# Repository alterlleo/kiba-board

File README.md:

# kiba-board
Truffle finder board

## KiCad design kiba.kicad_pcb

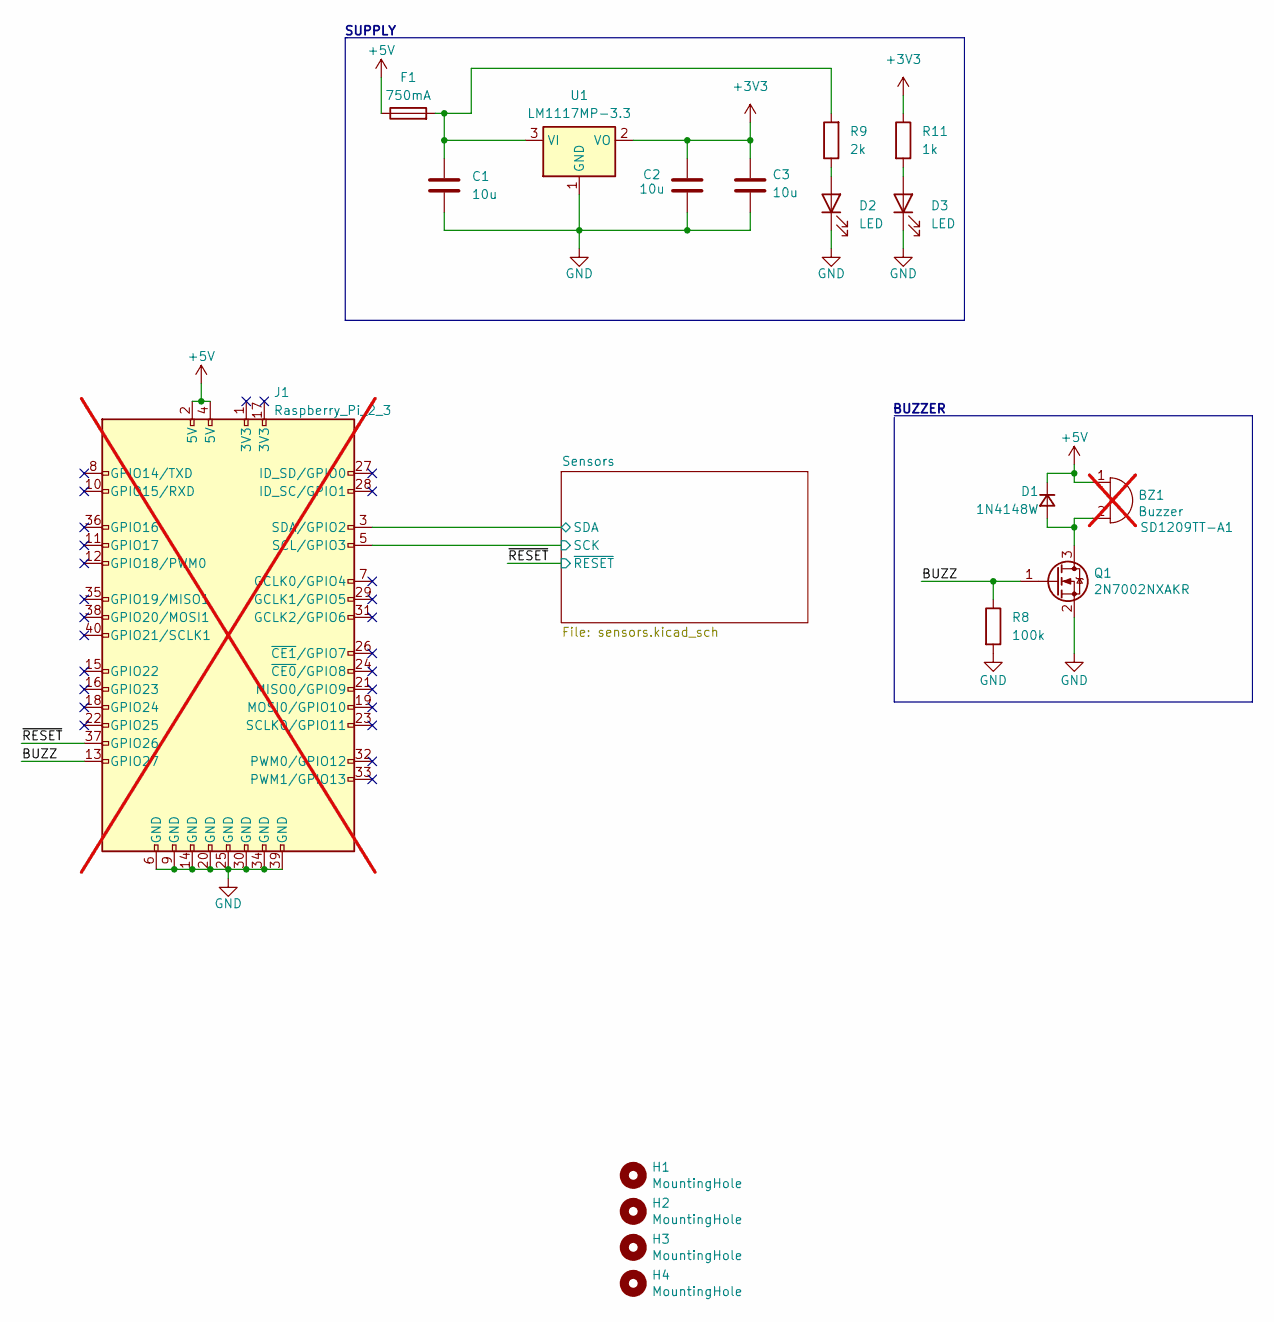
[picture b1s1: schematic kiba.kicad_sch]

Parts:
BZ1: Buzzer; Buzzer_TDK_PS1240P02BT_D12.2mm_H6.5mm; MPN SD1209TT-A1; LCSC C91083; not fitted
C1, C2, C3: 10u; C_0603_1608Metric
D1: 1N4148W; D_SOD-323_HandSoldering; MPN 1N4148W; LCSC C2099
D2: LED; D_0603_1608Metric; MPN TLMS1000-GS15; LCSC C2288
D3: LED; D_0603_1608Metric; MPN TLMS1000-GS15; LCSC C12624
F1: 750mA; Fuse_0603_1608Metric; LCSC C206991
H1, H2, H3, H4: MountingHole; MountingHole_3.2mm_M3_ISO14580
J1: Raspberry_Pi_2_3; raspberrypi; MPN 2.54-2*20; LCSC C2977589; not fitted
Q1: 2N7002NXAKR; SOT-23; MPN 2N7002NXAKR; LCSC C551416
R8: 100k; R_0603_1608Metric
R9: 2k; R_0603_1608Metric
R11: 1k; R_0603_1608Metric
U1: LM1117MP-3.3; SOT-223-3_TabPin2; MPN LM1117MP-3.3/TR; LCSC C498153

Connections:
+3V3: C2.1, C3.1, R11.1, U1.2 (VO); also elsewhere on the board
+5V: BZ1.1 (-), D1.1 (K), F1.1, J1.2 (5V), J1.4 (5V)
/BUZZ: J1.13 (GPIO27), Q1.1 (G), R8.1
/Sensors/SCK: J1.5 (SCL/GPIO3); also elsewhere on the board
/Sensors/SDA: J1.3 (SDA/GPIO2); also elsewhere on the board
/~RESET: J1.37 (GPIO26); also elsewhere on the board
GND: C1.2, C2.2, C3.2, D2.1 (K), D3.1 (K), J1.6 (GND), J1.9 (GND), J1.14 (GND), J1.20 (GND), J1.25 (GND), J1.30 (GND), J1.34 (GND), J1.39 (GND), Q1.2 (S), R8.2, U1.1 (GND); also elsewhere on the board
unnamed: BZ1.2 (+), D1.2 (A), Q1.3 (D)
unnamed: D2.2 (A), R9.1
unnamed: D3.2 (A), R11.2
unnamed: C1.1, F1.2, R9.2, U1.3 (VI)

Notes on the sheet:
SUPPLY
BUZZER

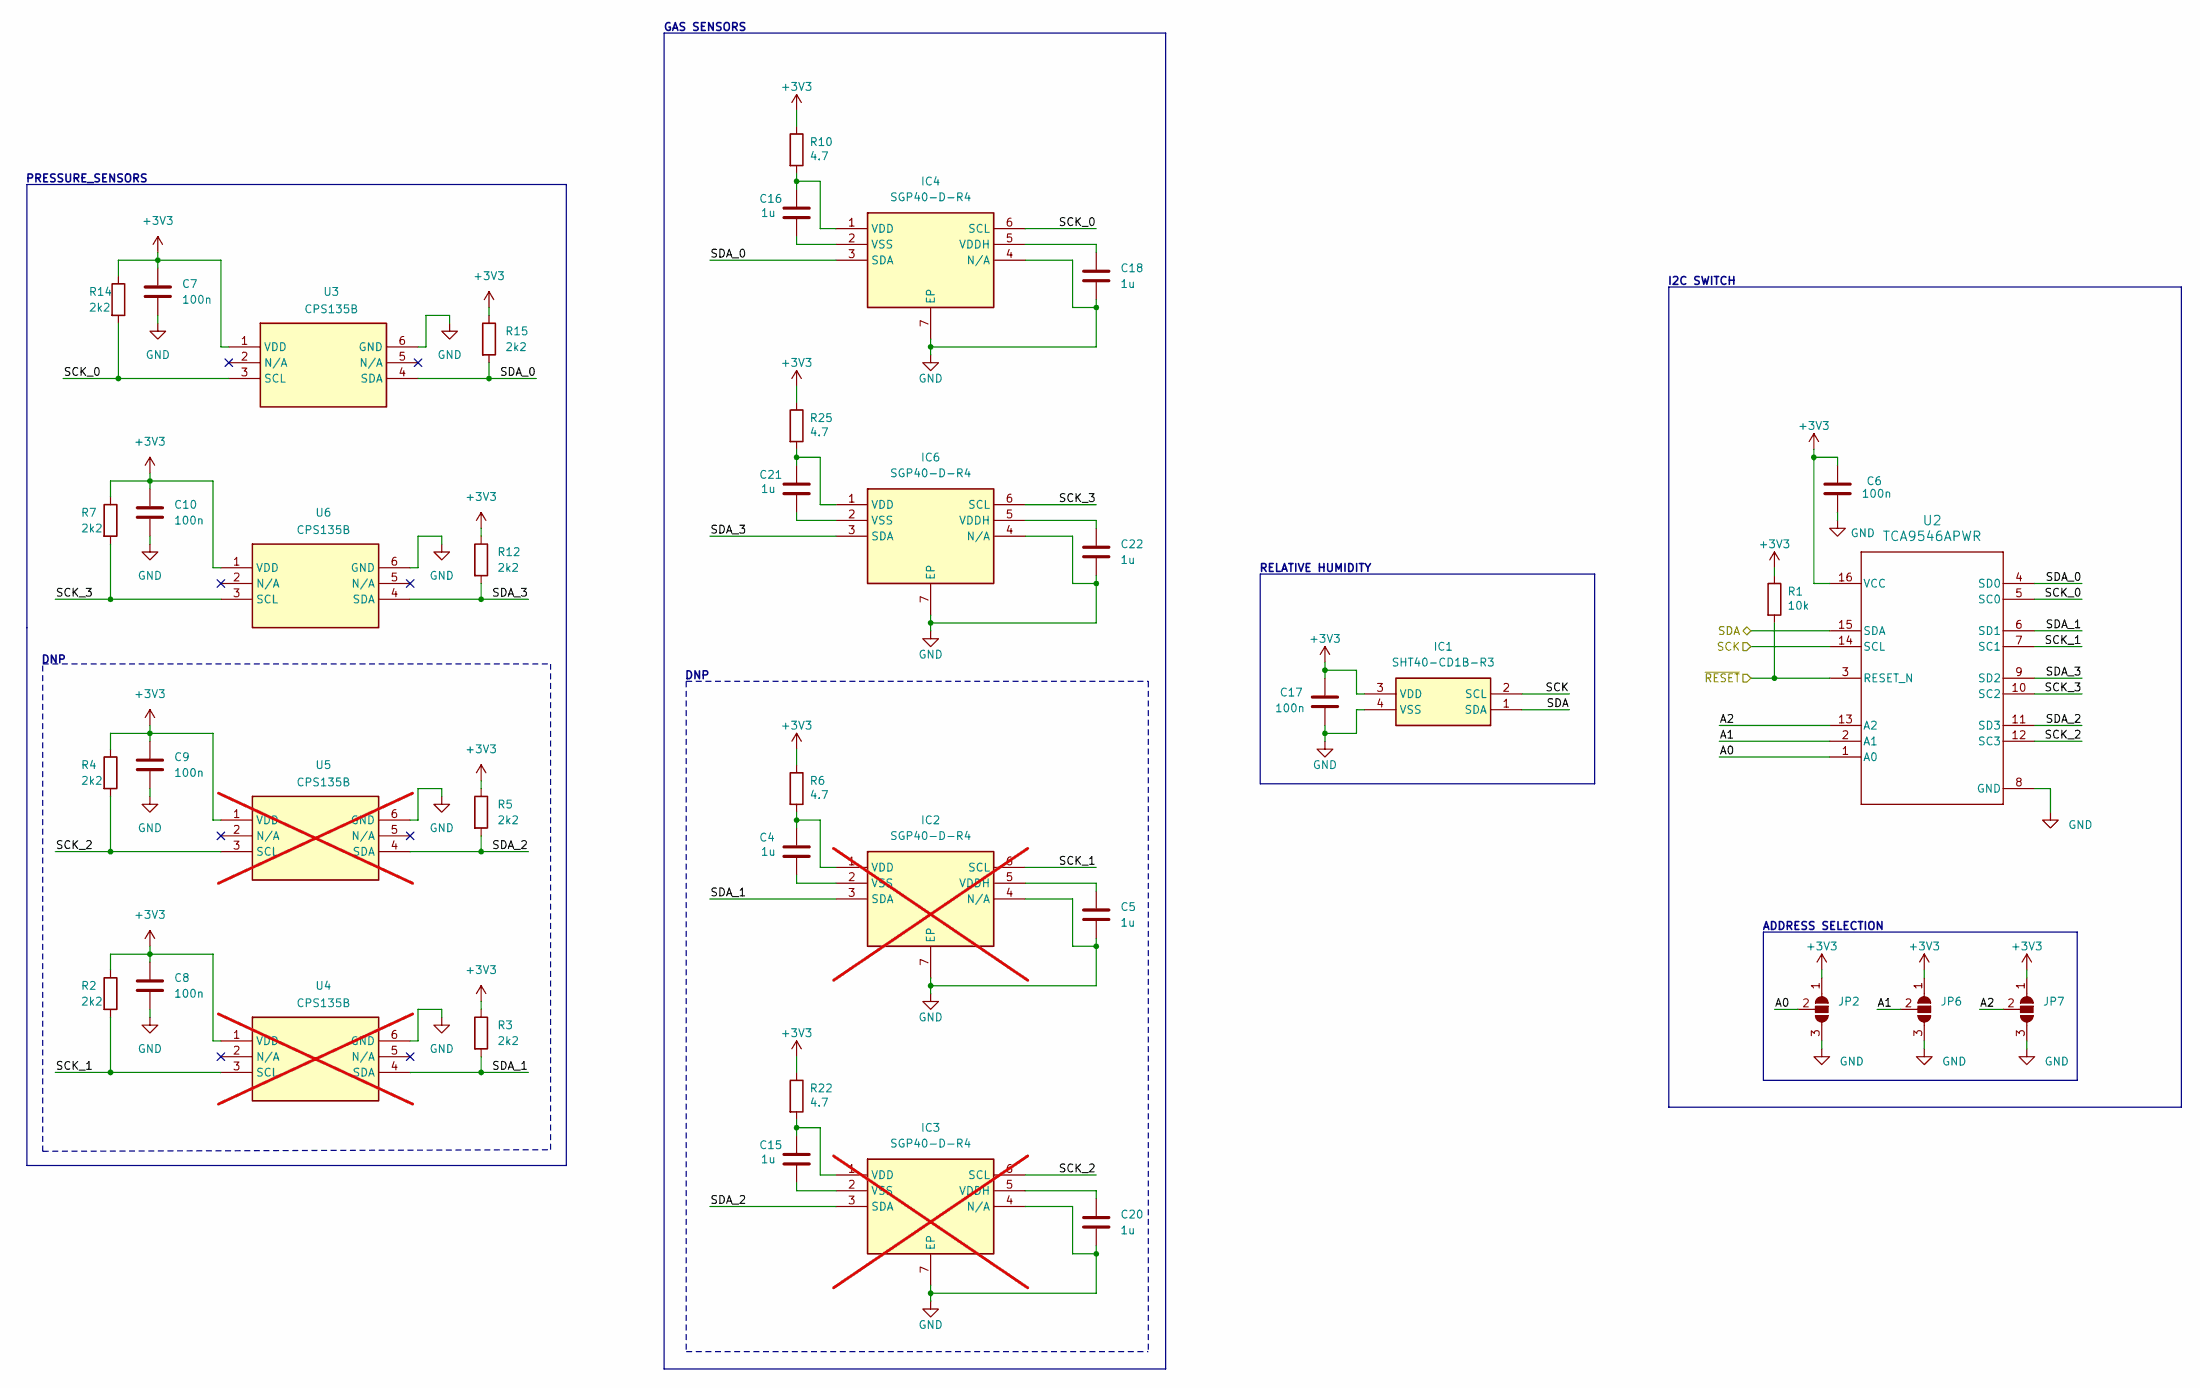
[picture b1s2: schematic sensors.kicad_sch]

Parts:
C4, C5, C15, C16, C18, C20, C21, C22: 1u; C_0603_1608Metric
C6, C7, C8, C9, C10, C17: 100n; C_0603_1608Metric
IC1: SHT40-CD1B-R3; SHT40CD1BR3; Mouser Part Number 403-SHT40-CD1B-R3
IC2, IC3: SGP40-D-R4; SON80P244X244X95-7N; Mouser Part Number 403-SGP40-D-R4; not fitted
IC4, IC6: SGP40-D-R4; SON80P244X244X95-7N; Mouser Part Number 403-SGP40-D-R4
JP2, JP6, JP7: SolderJumper_3_Open; SolderJumper-3_P1.3mm_Open_RoundedPad1.0x1.5mm
R1: 10k; R_0603_1608Metric
R2, R3, R4, R5, R7, R12, R14, R15: 2k2; R_0603_1608Metric
R6, R10, R22, R25: 4.7; R_0603_1608Metric
U2: TCA9546APWR; PW0016A-IPC_A; LCSC C201653
U3, U6: CPS135B; smd6-4.5mm; LCSC C491452
U4, U5: CPS135B; smd6-4.5mm; LCSC C491452; not fitted

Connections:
+3V3: C6.1, C7.1, C8.1, C9.1, C10.1, C17.1, IC1.3 (VDD), JP2.1 (A), JP6.1 (A), JP7.1 (A), R1.1, R2.1, R3.1, R4.1, R5.1, R6.1, R7.1, R10.1, R12.1, R14.1, R15.1, R22.1, R25.1, U2.16 (VCC), U3.1 (VDD), U4.1 (VDD), U5.1 (VDD), U6.1 (VDD); also elsewhere on the board
/Sensors/A0: JP2.2 (C), U2.1 (A0)
/Sensors/A1: JP6.2 (C), U2.2 (A1)
/Sensors/A2: JP7.2 (C), U2.13 (A2)
/Sensors/SCK: IC1.2 (SCL), U2.14 (SCL); also elsewhere on the board
/Sensors/SCK_0: IC4.6 (SCL), R14.2, U2.5 (SC0), U3.3 (SCL)
/Sensors/SCK_1: IC2.6 (SCL), R2.2, U2.7 (SC1), U4.3 (SCL)
/Sensors/SCK_2: IC3.6 (SCL), R4.2, U2.12 (SC3), U5.3 (SCL)
/Sensors/SCK_3: IC6.6 (SCL), R7.2, U2.10 (SC2), U6.3 (SCL)
/Sensors/SDA: IC1.1 (SDA), U2.15 (SDA); also elsewhere on the board
/Sensors/SDA_0: IC4.3 (SDA), R15.2, U2.4 (SD0), U3.4 (SDA)
/Sensors/SDA_1: IC2.3 (SDA), R3.2, U2.6 (SD1), U4.4 (SDA)
/Sensors/SDA_2: IC3.3 (SDA), R5.2, U2.11 (SD3), U5.4 (SDA)
/Sensors/SDA_3: IC6.3 (SDA), R12.2, U2.9 (SD2), U6.4 (SDA)
/~RESET: R1.2, U2.3 (RESET_N); also elsewhere on the board
GND: C5.2, C6.2, C7.2, C8.2, C9.2, C10.2, C17.2, C18.2, C20.2, C22.2, IC1.4 (VSS), IC2.4 (N/A), IC2.7 (EP), IC3.4 (N/A), IC3.7 (EP), IC4.4 (N/A), IC4.7 (EP), IC6.4 (N/A), IC6.7 (EP), JP2.3 (B), JP6.3 (B), JP7.3 (B), U2.8 (GND), U3.6 (GND), U4.6 (GND), U5.6 (GND), U6.6 (GND); also elsewhere on the board
unnamed: C4.1, IC2.1 (VDD), R6.2
unnamed: C5.1, IC2.5 (VDDH)
unnamed: C4.2, IC2.2 (VSS)
unnamed: C15.1, IC3.1 (VDD), R22.2
unnamed: C20.1, IC3.5 (VDDH)
unnamed: C15.2, IC3.2 (VSS)
unnamed: C16.1, IC4.1 (VDD), R10.2
unnamed: C18.1, IC4.5 (VDDH)
unnamed: C16.2, IC4.2 (VSS)
unnamed: C21.1, IC6.1 (VDD), R25.2
unnamed: C22.1, IC6.5 (VDDH)
unnamed: C21.2, IC6.2 (VSS)

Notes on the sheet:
GAS SENSORS
I2C SWITCH
DNP
ADDRESS SELECTION
RELATIVE HUMIDITY
PRESSURE_SENSORS

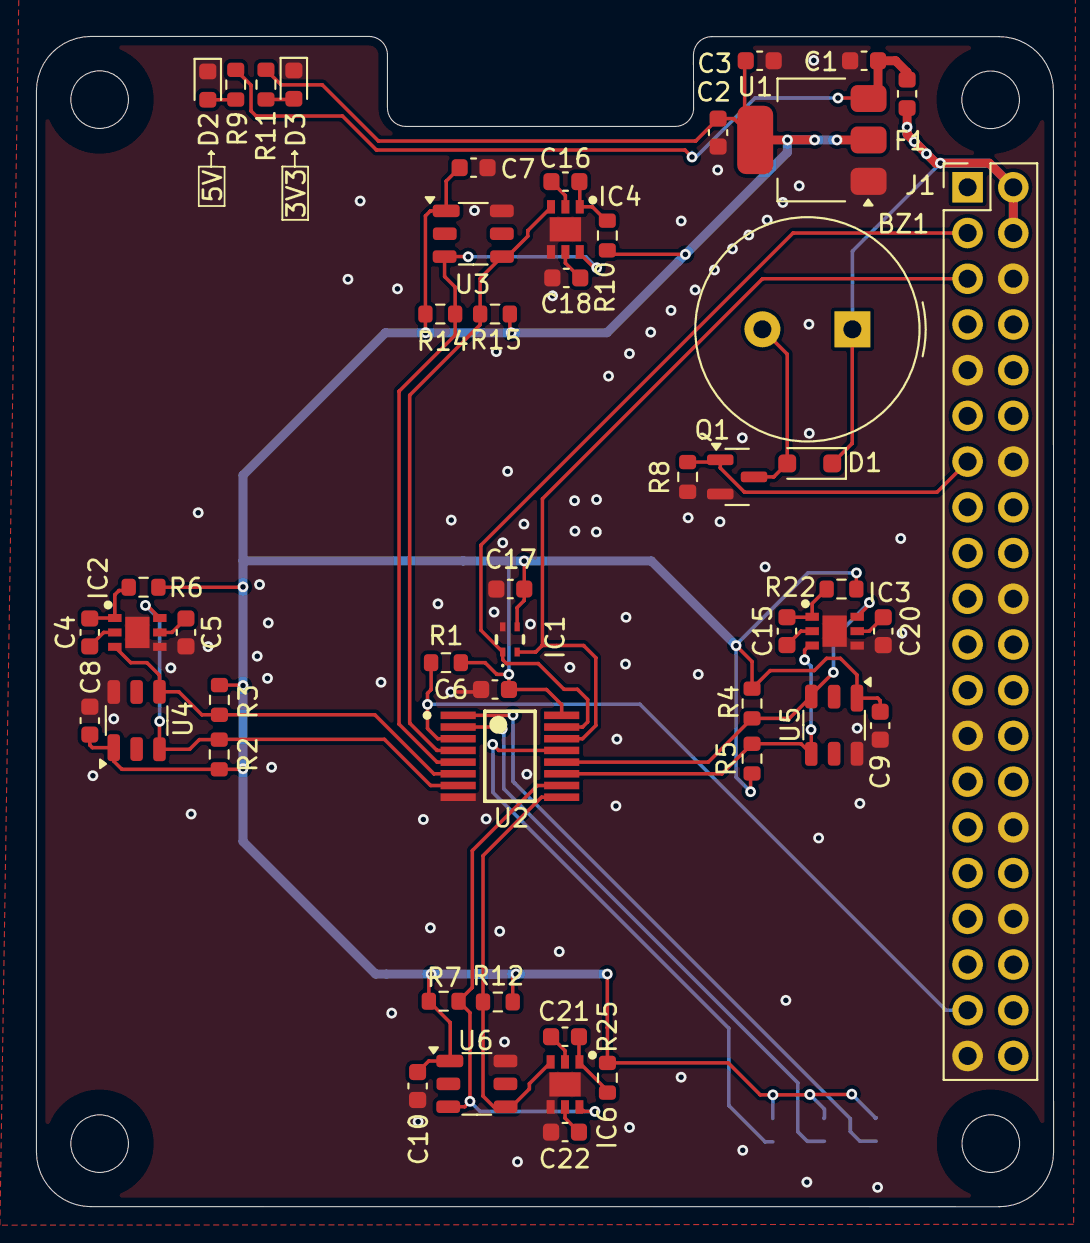
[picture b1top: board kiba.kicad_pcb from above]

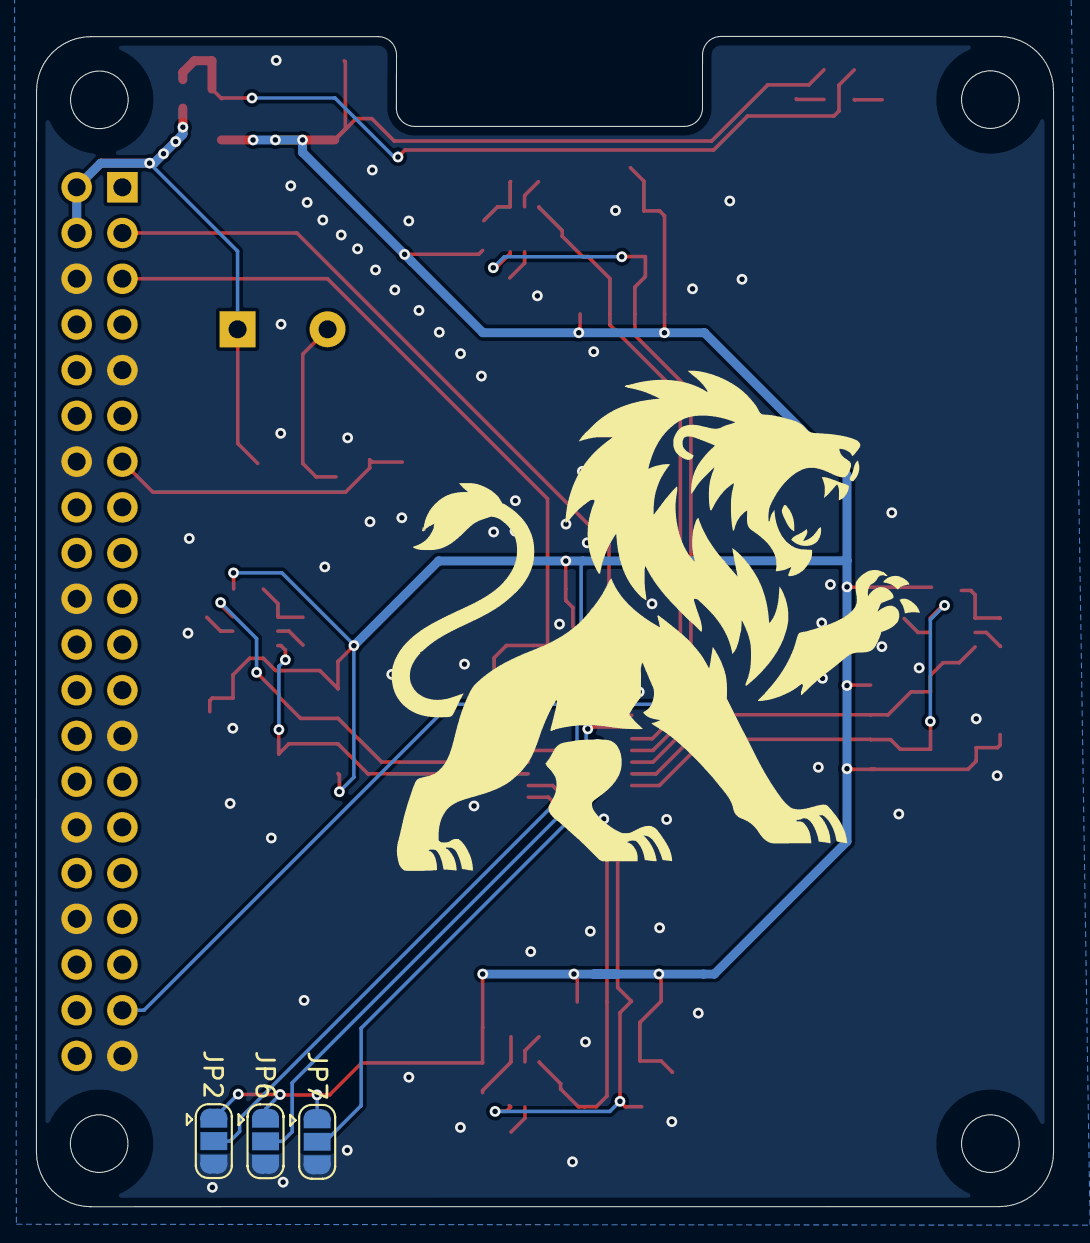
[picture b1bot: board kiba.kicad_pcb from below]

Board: 2 copper layers, 56.5 x 65.0 mm, 58 parts (3 on the bottom side), 34 nets.

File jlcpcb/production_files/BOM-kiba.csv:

Comment,Designator,Footprint,LCSC,Quantity
LED,D3,D_0603_1608Metric,C12624,1
TCA9546APWR,U2,PW0016A-IPC_A,C201653,1
750mA,F1,Fuse_0603_1608Metric,C206991,1
1N4148W,D1,D_SOD-323_HandSoldering,C2099,1
LED,D2,D_0603_1608Metric,C2288,1
SGP40-D-R4,"IC4,IC6",SON80P244X244X95-7N,C2874215,2
CPS135B,"U3,U6",smd6-4.5mm,C491452,2
LM1117MP-3.3,U1,SOT-223-3_TabPin2,C498153,1
2N7002NXAKR,Q1,SOT-23,C551416,1
SHT40-CD1B-R3,IC1,SHT40CD1BR3,C7461852,1
4.7,R10,R_0603_1608Metric,,1
2k2,R3,R_0603_1608Metric,,1
1u,C5,C_0603_1608Metric,,1
2k2,R15,R_0603_1608Metric,,1
1k,R11,R_0603_1608Metric,,1
100n,C9,C_0603_1608Metric,,1
2k2,R4,R_0603_1608Metric,,1
1u,C18,C_0603_1608Metric,,1
4.7,R6,R_0603_1608Metric,,1
10u,C3,C_0603_1608Metric,,1
10u,C2,C_0603_1608Metric,,1
1u,C20,C_0603_1608Metric,,1
4.7,R22,R_0603_1608Metric,,1
100k,R8,R_0603_1608Metric,,1
100n,C17,C_0603_1608Metric,,1
1u,C21,C_0603_1608Metric,,1
1u,C22,C_0603_1608Metric,,1
2k2,R14,R_0603_1608Metric,,1
1u,C4,C_0603_1608Metric,,1
100n,C10,C_0603_1608Metric,,1
2k,R9,R_0603_1608Metric,,1
1u,C15,C_0603_1608Metric,,1
100n,C7,C_0603_1608Metric,,1
10u,C1,C_0603_1608Metric,,1
1u,C16,C_0603_1608Metric,,1
100n,C6,C_0603_1608Metric,,1
4.7,R25,R_0603_1608Metric,,1
100n,C8,C_0603_1608Metric,,1
10k,R1,R_0603_1608Metric,,1
2k2,R12,R_0603_1608Metric,,1
2k2,R5,R_0603_1608Metric,,1
2k2,R2,R_0603_1608Metric,,1
2k2,R7,R_0603_1608Metric,,1

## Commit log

2025-08-29 feat: add sensors libraries
2025-08-29 feat: initial setup
2025-08-29 feat: add gitignore
2025-08-29 fix: bmp581 config
2025-08-30 feat: add buzzer
2025-08-30 feat: new configuration with i2c switch
2025-08-30 fix: cleanup
2025-08-31 fix: arrange board for a total of 8 sensors, 4 DNP
2025-08-31 feat: address selection i2c switch
2025-08-31 feat: rasp connections + fan
2025-08-31 fix: missing footprints
2025-09-02 fix: missing save and add leds + fuse on power supply
2025-09-02 fix: fllags and footprints
2025-09-02 feat: pcb first draft
2025-09-02 feat: first sensors couple connected
2025-09-02 feat: first pcb draft completed
2025-09-02 fix: drc errors
2025-09-02 fix: silkscreen
2025-09-02 feat: add license
2025-09-03 fix: missing 3d models
2025-09-03 fix: 4 channels i2c switch
2025-09-03 feat: add RH sensor
2025-09-04 fix: gnd zones clearane decreased
2025-09-04 fix: minors
2025-09-06 fix: unused i2c pullups
2025-09-06 fix: i2c layout with vias
2025-09-06 fix: dnp in opposite edges
2025-09-07 feat: pullup resistors values
2025-09-07 fix: pullup resistors layout
2025-09-07 prod: add MPN
2025-09-08 Added JLCPCB part numbers and generated BOM
2025-09-08 fix: cps135b as new barometer
2025-09-12 production files for jlcpcb, added passives for DNP sensors
